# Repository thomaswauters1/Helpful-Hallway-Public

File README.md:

# Helpful Hallway

This repository has all files of the Helpful Hallway project used for the Embedded systems II lab.
All code is represented in the seperate parts 

## Report
[Download pdf](https://github.com/thomaswauters1/Helpful-Hallway-Public/raw/master/Report_HelpfulHallway.pdf)
## Hardware
[PCB](https://github.com/thomaswauters1/Helpful-Hallway-Public/tree/master/Hardware)  
## Software
[Audio](https://github.com/thomaswauters1/Helpful-Hallway-Public/tree/master/Code_Audio_sensor)  
[IR Camera](https://github.com/thomaswauters1/Helpful-Hallway-Public/tree/master/Code_IR_sensor)  
[Connectivity](https://github.com/thomaswauters1/Helpful-Hallway-Public/tree/master/Code_Communication)  
[Server](https://github.com/thomaswauters1/Helpful-Hallway-Public/tree/master/CodeRaspberryPi)

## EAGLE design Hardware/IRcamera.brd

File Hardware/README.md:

# Hardware
All files for the design of the main PCB and the IR-camera PCB are available here.
These schematics are designed in Eagle.

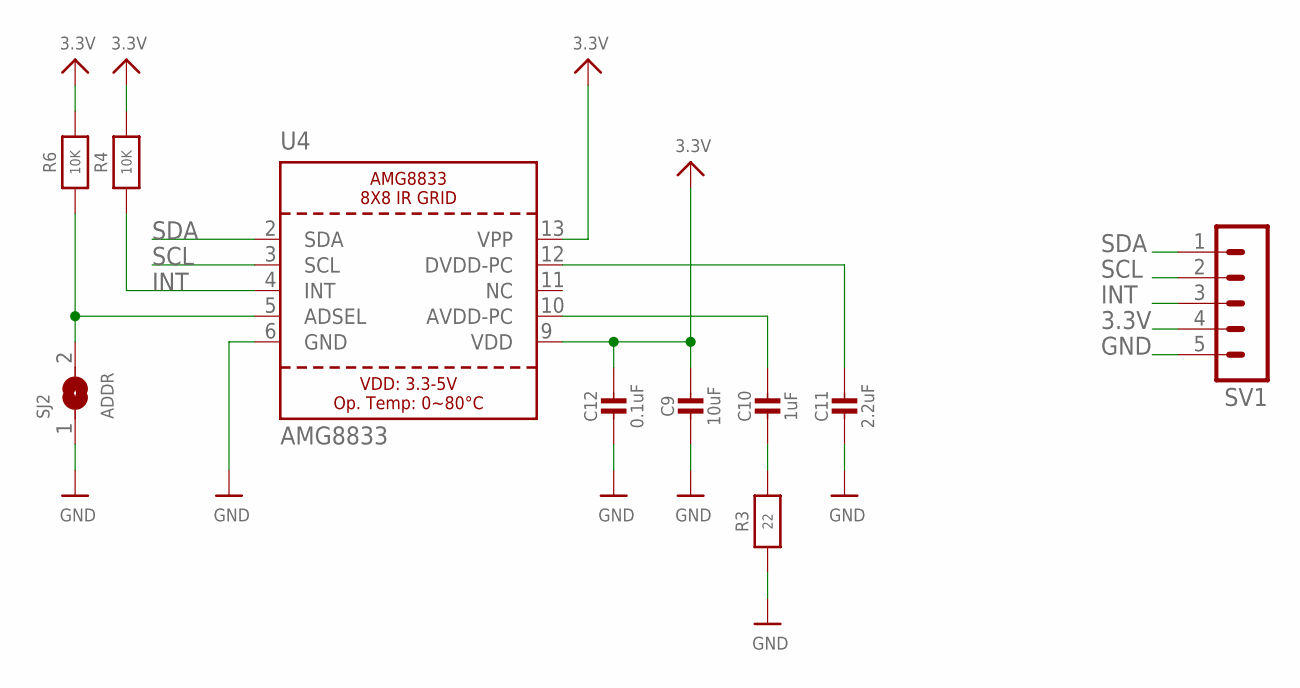
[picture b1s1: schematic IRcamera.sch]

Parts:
C9: 10uF; 0805-NO
C10: 1uF; 0805-NO
C11: 2.2uF; 0805-NO
C12: 0.1uF; 0805-NO
R3: 22; 0805-NO
R4, R6: 10K; 0805-NO
SJ2: ADDR; SOLDERJUMPER_ARROW_NOPASTE
SV1: MA05-1
U4: AMG8833

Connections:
3.3V: C9.1, C12.1, R4.2, R6.2, SV1.4, U4.9 (VDD), U4.13 (VPP)
AVDD-PC1: C10.1, U4.10 (AVDD-PC)
DVDD-PC1: C11.1, U4.12 (DVDD-PC)
GND: C9.2, C11.2, C12.2, R3.1, SJ2.1, SV1.5, U4.6 (GND)
INT: R4.1, SV1.3, U4.4 (INT)
unnamed: R6.1, SJ2.2, U4.5 (ADSEL)
unnamed: C10.2, R3.2
SCL: SV1.2, U4.3 (SCL)
SDA: SV1.1, U4.2 (SDA)

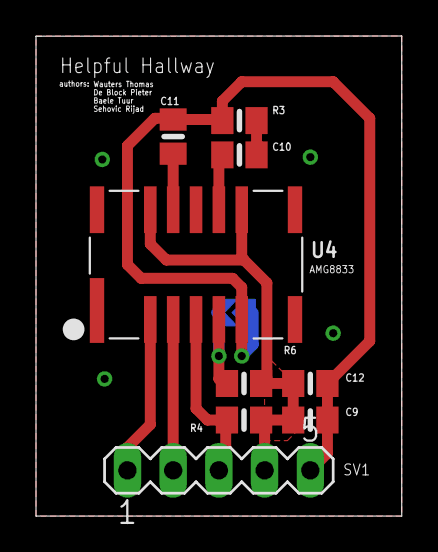
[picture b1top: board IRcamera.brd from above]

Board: 2 copper layers, 20.3 x 26.7 mm, 10 parts (1 on the bottom side), 9 nets.

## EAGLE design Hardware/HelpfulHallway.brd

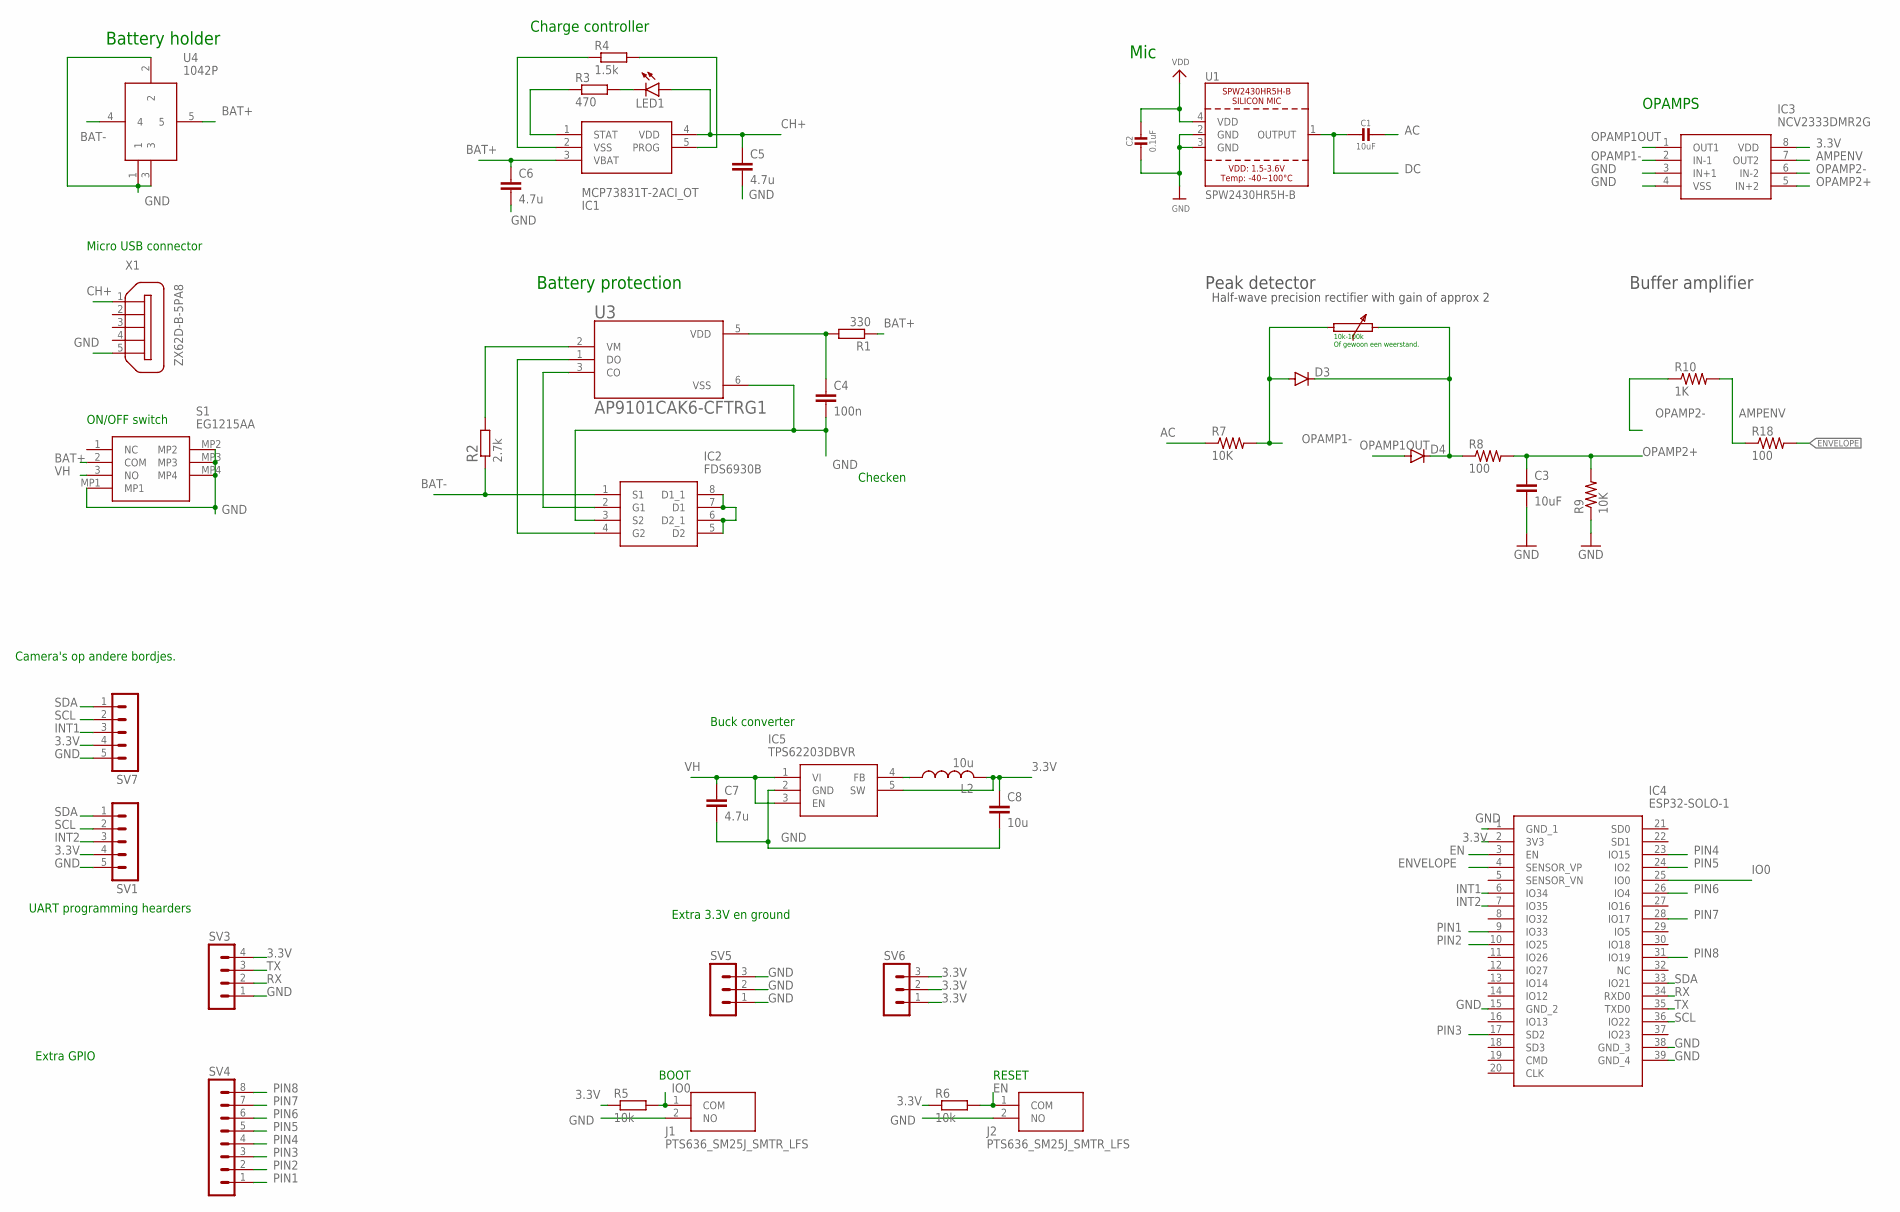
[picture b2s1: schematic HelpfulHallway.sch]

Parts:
C1: 10uF; 0805-NO
C2: 0.1uF; 0805-NO
C3: 10uF; 1206
C4: 100n; C1206
C5, C6, C7: 4.7u; C1206
C8: 10u; C1206
D3, D4: DIODE-SOD123; SOD123
IC1: MCP73831T-2ACI_OT; SOT95P270X145-5N
IC2: FDS6930B; SOIC127P600X175-8N
IC3: NCV2333DMR2G; SOP65P490X110-8N
IC4: ESP32-SOLO-1; ESP32SOLO1
IC5: TPS62203DBVR; SOT95P280X145-5N
J1, J2: PTS636_SM25J_SMTR_LFS; PTS636SM25JSMTRLFS
L2: 10u; L4532P
LED1: LEDSMT1206; 1206
R1: 330; R1206
R2: 2.7k; R1206
R3: 470; R1206
R4: 1.5k; R1206
R5, R6: 10k; M1206
R7, R9: 10K; 0603-RES
R8, R18: 100; 0603-RES
R10: 1K; 0603-RES
S1: EG1215AA
SV1, SV7: MA05-1
SV3: MA04-1
SV4: MA08-1
SV5, SV6: MA03-1
U1: SPW2430HR5H-B
U3: AP9101CAK6-CFTRG1; SOT95P280X140-6N
U4: 1042P
X1: ZX62D-B-5PA8

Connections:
3.3V: C8.1, IC3.8 (VDD), IC4.2 (3V3), IC5.5 (SW), L2.2, R5.1, R6.1, SV1.4, SV3.4, SV6.1, SV6.2, SV6.3, SV7.4
AC: C1.1, R7.1
AMPENV: IC3.7 (OUT2), R10.2, R18.1
BAT+: C6.1, IC1.3 (VBAT), R1.1, S1.2 (COM), U4.5
BAT-: IC2.1 (S1), R2.1, U4.4
CH+: C5.1, IC1.4 (VDD), LED1.A, X1.1
DC: C1.2, U1.1 (OUTPUT)
EN: IC4.3 (EN), J2.1 (COM), R6.2
ENVELOPE: IC4.4 (SENSOR_VP), R18.2
GND: C2.2, C3.2, C4.2, C5.2, C6.2, C7.2, C8.2, IC2.3 (S2), IC3.3 (IN+1), IC3.4 (VSS), IC4.1 (GND_1), IC4.15 (GND_2), IC4.38 (GND_3), IC4.39 (GND_4), IC5.2 (GND), J1.2 (NO), J2.2 (NO), R9.1, S1.MP1, S1.MP2, S1.MP3, S1.MP4, SV1.5, SV3.1, SV5.1, SV5.2, SV5.3, SV7.5, U1.2 (GND), U1.3 (GND), U3.6 (VSS), U4.1, U4.2, U4.3, X1.5
INT1: IC4.6 (IO34), SV7.3
INT2: IC4.7 (IO35), SV1.3
IO0: IC4.25 (IO0), J1.1 (COM), R5.2
unnamed: R2.2, U3.2 (VM)
unnamed: IC2.5 (D2), IC2.6 (D2_1), IC2.7 (D1), IC2.8 (D1_1)
unnamed: IC2.4 (G2), U3.1 (DO)
unnamed: IC2.2 (G1), U3.3 (CO)
unnamed: LED1.C, R3.2
unnamed: C4.1, R1.2, U3.5 (VDD)
unnamed: D3.C, D4.C, R8.1
unnamed: IC1.1 (STAT), R3.1
unnamed: IC5.4 (FB), L2.1
unnamed: IC1.5 (PROG), R4.2
unnamed: IC1.2 (VSS), R4.1
OPAMP1-: D3.A, IC3.2 (IN-1), R7.2
OPAMP1OUT: D4.A, IC3.1 (OUT1)
OPAMP2+: C3.1, IC3.5 (IN+2), R8.2, R9.2
OPAMP2-: IC3.6 (IN-2), R10.1
PIN1: IC4.9 (IO33), SV4.1
PIN2: IC4.10 (IO25), SV4.2
PIN3: IC4.17 (SD2), SV4.3
PIN4: IC4.23 (IO15), SV4.4
PIN5: IC4.24 (IO2), SV4.5
PIN6: IC4.26 (IO4), SV4.6
PIN7: IC4.28 (IO17), SV4.7
PIN8: IC4.31 (IO19), SV4.8
RX: IC4.34 (RXD0), SV3.2
SCL: IC4.36 (IO22), SV1.2, SV7.2
SDA: IC4.33 (IO21), SV1.1, SV7.1
TX: IC4.35 (TXD0), SV3.3
VDD: C2.1, U1.4 (VDD)
VH: C7.1, IC5.1 (VI), IC5.3 (EN), S1.3 (NO)

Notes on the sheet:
Mic
Camera's op andere bordjes.
Peak detector
Buffer amplifier
Half-wave precision rectifier with gain of approx 2
Battery holder
10k-100k Of gewoon een weerstand.
OPAMPS
UART programming hearders
Extra GPIO
Battery protection
Charge controller
ON/OFF switch
Micro USB connector
Checken
Buck converter
Extra 3.3V en ground
BOOT
RESET

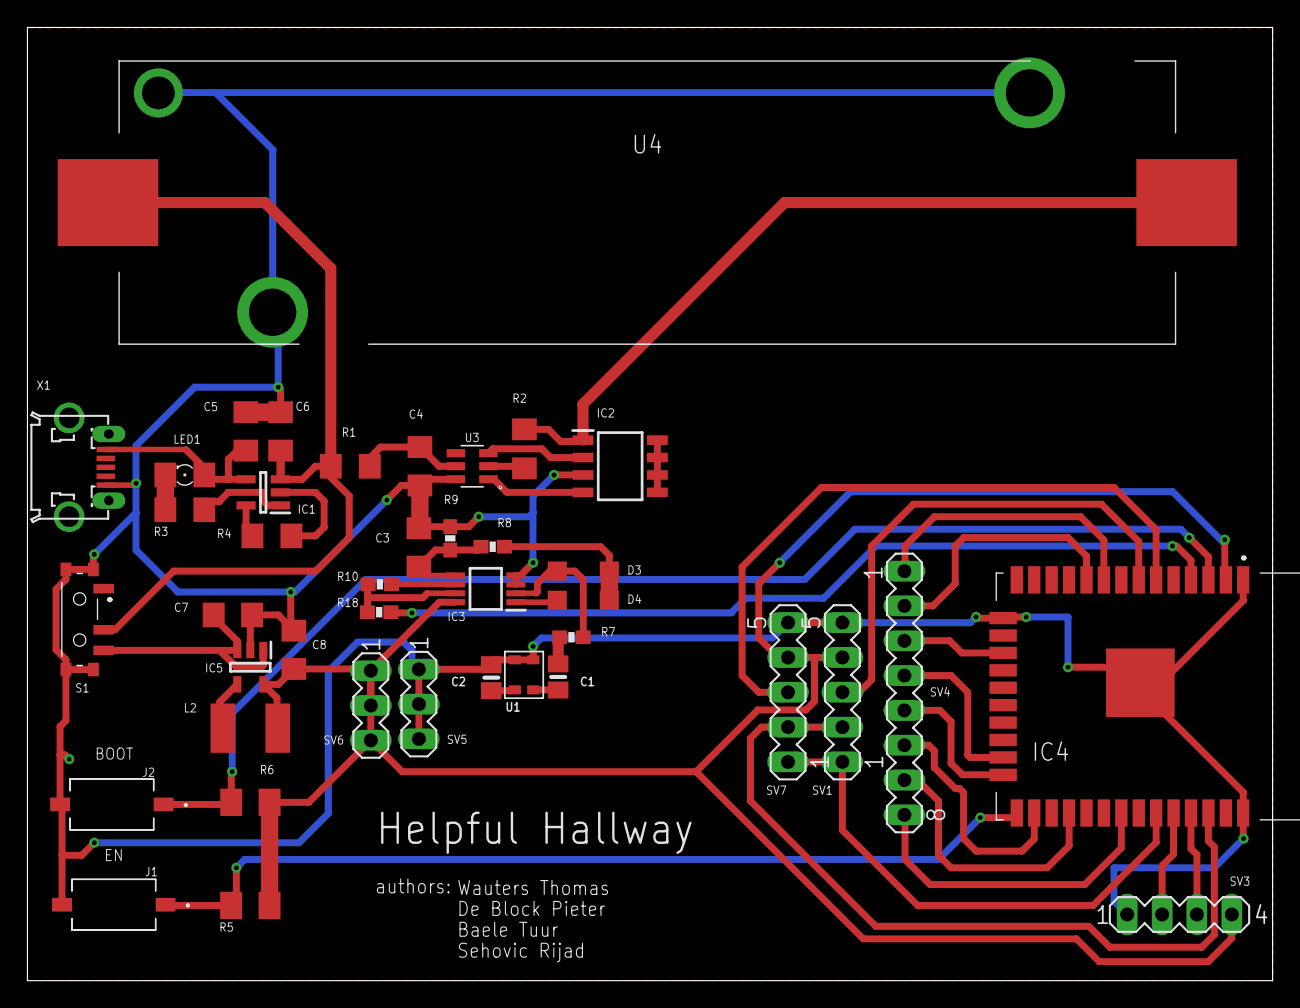
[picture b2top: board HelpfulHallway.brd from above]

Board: 2 copper layers, 90.8 x 69.5 mm, 41 parts (0 on the bottom side), 42 nets.

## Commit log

2020-05-06 folder changes
2020-05-06 Folder Change
2020-05-06 Final Version
2020-07-21 Added presentation
    Final commit so I can delete this from my drive

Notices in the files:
parts and their libraries:
microbuilder: This work is placed in the public domain, and may be freely used for commercial and non-commercial work with the following conditions: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
SparkFun-Capacitors: Licensing: CC v3.0 Share-Alike You are welcome to use this library for commercial purposes.
